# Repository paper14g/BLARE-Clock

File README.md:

# BLARE-Clock
This is my first ever Hack Club project! I should have chosen keeb because this is intermediate, but it is what it is.

this is CatClock, a clock that looks like a cat! except a screeching cat that will wake you up. I used Onshape to do the CAD designing work and I used Arduino IDE in order to code the firmware for the clock that will tell the time. Since I don't have a physical kit at the time of this typing, I will hope that it works first try. CAD designing was tricky at first because I never used it before. It took about 6-7 hours total and It was definitely very tricky.

This is my schematic, which shows an idea of how the parts are connected

This is my PCB, which will be custom made to fit my clock

As you can see, the PCB is held up by the supports inside the case and fit snugly in there with some screws to keep in place. The screen will also be inserted into a slot with a small hole behind it for connecting the the PCB.

There was some AI usage to assist me with KiCad footprint troubleshooting, OnShape tools, and some of the coding since I am unfamiliar with the coding language.

ONSHAPE LINK: https://cad.onshape.com/documents/35f3ca1c154542e0a4ea4d61/w/57b5bd0aad0669b366a0d6c3/e/0ef1ebbdd80ca3363562ccff?renderMode=0&uiState=6ac0b07b7f23611b255fec3d
 
I believe the guide asks me to put my Bill Of Materials here, so it's just a copy and paste.

|Designator|Quantity|Component Name|Footprint|Sourcing Link|
|---|---|---|---|---|
|U1|1|XIAO ESP32-C3|foot:XIAO-ESP32-C3-DIP|https://www.seeedstudio.com/Seeed-XIAO-ESP32C3-p-5431.html?srsltid=AU7gw4VDwjUAIm7gTielzF3R162CpobM-U2K9dWKoW9xlxCvq-3HqC8obDw
|SW1,SW2,SW3,SW4|4|Cherry MX Compatible Key Switch|switch:SW_Cherry_MX_1.00u_PCB|https://panda-mousepads.com/products/cherry-mx-mechanical-keyboard-switches-3-pin?variant=40930875670691&country=US&currency=USD&utm_medium=product_sync&utm_source=google&utm_content=sag_organic&utm_campaign=sag_organic&srsltid=AU7gw4UjE_LDTER6We5ZA6FkqacR6w-Ml-_MZT-fGag7CERpbxS0HlY9h4A
|J1|1|8-Pin 2.54mm Female Header Socket|connector:PinSocket_1x08_P2.54mm_Vertical|https://www.aliexpress.us/item/3256807486796996.html?spm=a2g0o.productlist.main.3.5654RBBuRBBuQy&algo_pvid=d6e48885-06fc-4b73-9e46-34dd52416a54&algo_exp_id=d6e48885-06fc-4b73-9e46-34dd52416a54-2&pdp_ext_f=%7B%22order%22%3A%22895%22%2C%22eval%22%3A%221%22%2C%22fromPage%22%3A%22search%22%7D&pdp_npi=6%40dis%21USD%212.60%211.09%21%21%212.60%211.09%21%402101ef5e17900453187957766e0eda%2112000041751476406%21sea%21US%210%21ABX%211%210%21n_tag%3A-29910%3Bd%3A982aa020%3Bm03_new_user%3A-29895%3BpisId%3A5000000210788688&curPageLogUid=JY7H0YBLu0v3&utparam-url=scene%3Asearch%7Cquery_from%3A%7Cx_object_id%3A1005007673111748%7C_p_origin_prod%3A
|BZ1|1|5V Passive Buzzer (12mm)|buzzer:Buzzer_12x9.5RM7.6|https://www.aliexpress.us/item/3256812304653037.html?spm=a2g0o.productlist.main.2.7167bTGybTGyND&algo_pvid=3d12822e-bb3b-4dd3-806f-8355b4d0be10&algo_exp_id=3d12822e-bb3b-4dd3-806f-8355b4d0be10-1&pdp_ext_f=%7B%22order%22%3A%2214%22%2C%22eval%22%3A%221%22%2C%22fromPage%22%3A%22search%22%7D&pdp_npi=6%40dis%21USD%214.26%211.09%21%21%2128.33%217.20%21%402103094f17900453807931080e130e%2112000058544450596%21sea%21US%210%21ABX%211%210%21n_tag%3A-29910%3Bd%3A982aa020%3Bm03_new_user%3A-29895%3BpisId%3A5000000210788678&curPageLogUid=0Z9NItkvW6ou&utparam-url=scene%3Asearch%7Cquery_from%3A%7Cx_object_id%3A1005012490967789%7C_p_origin_prod%3A
|J1|1|1.3 Inch Rectangular TFT LCD Module|connector:PinSocket_1x08_P2.54mm_Vertical|https://www.aliexpress.us/item/3256809161612031.html?spm=a2g0o.productlist.main.2.7c30OCHbOCHbqt&algo_pvid=e0094769-9c7d-42a3-a7c9-ebd94f11fb5c&algo_exp_id=e0094769-9c7d-42a3-a7c9-ebd94f11fb5c-1&pdp_ext_f=%7B%22order%22%3A%221138%22%2C%22eval%22%3A%221%22%2C%22fromPage%22%3A%22search%22%7D&pdp_npi=6%40dis%21USD%2171.88%2127.94%21%21%21478.56%21186.02%21%402101d9ef17900458449312800e0edc%2112000048828156242%21sea%21US%210%21ABX%211%210%21n_tag%3A-29910%3Bd%3A982aa020%3Bm03_new_user%3A-29895%3BpisId%3A5000000210788678&curPageLogUid=rcA0dcdMAjqR&utparam-url=scene%3Asearch%7Cquery_from%3A%7Cx_object_id%3A1005009347926783%7C_p_origin_prod%3A
|Hardware|4|M3 Brass Heat-Set Inserts & Screws|4.7mm CAD Hole|https://www.aliexpress.us/item/2255800046543591.html
|Screws (Short)|4|M3 x 8mm Button Head Machine Screws|M3 Clearance Hole|https://www.aliexpress.us/item/3256806191432536.html?spm=a2g0o.productlist.main.20.8e105e55iEFuXx&utparam-url=scene%3Asearch%7Cquery_from%3Apc_back_same_best%7Cx_object_id%3A1005006377747288%7C_p_origin_prod%3A&algo_pvid=7987ab63-8d65-465a-ab5c-b03ca118e8df&algo_exp_id=7987ab63-8d65-465a-ab5c-b03ca118e8df&pdp_ext_f=%7B%22order%22%3A%222140%22%2C%22fromPage%22%3A%22search%22%7D&pdp_npi=6%40dis%21USD%210.76%210.53%21%21%215.03%213.52%21%402103094f17900462549591222e1350%2112000036956444828%21sea%21US%210%21ABX%211%210%21n_tag%3A-29910%3Bd%3A73118c74%3Bm03_new_user%3A-29895&gatewayAdapt=4itemAdapt
|Screws (Long)|4|M3 x 16mm Button Head Machine Screws|M3 Clearance Hole|https://www.aliexpress.us/item/2251832772825104.html?spm=a2g0o.productlist.main.2.7e535d68fF4aoG&algo_pvid=b0ebe1dd-e0fd-461d-bdbb-e06f6866e78d&algo_exp_id=b0ebe1dd-e0fd-461d-bdbb-e06f6866e78d-1&pdp_ext_f=%7B%22order%22%3A%22308%22%2C%22eval%22%3A%221%22%2C%22fromPage%22%3A%22search%22%7D&pdp_npi=6%40dis%21USD%212.85%211.09%21%21%2118.96%217.24%21%402101dedf17900463106434580e10ea%2166368903762%21sea%21US%210%21ABX%211%210%21n_tag%3A-29910%3Bd%3A982aa020%3Bm03_new_user%3A-29895%3BpisId%3A5000000210788688&curPageLogUid=jL92MpLTxxYn&utparam-url=scene%3Asearch%7Cquery_from%3A%7Cx_object_id%3A32959139856%7C_p_origin_prod%3A
|Case|1|Custom 3D Printed Enclosure|/CAD/catclockCAD.step|N/A (Self-Designed)

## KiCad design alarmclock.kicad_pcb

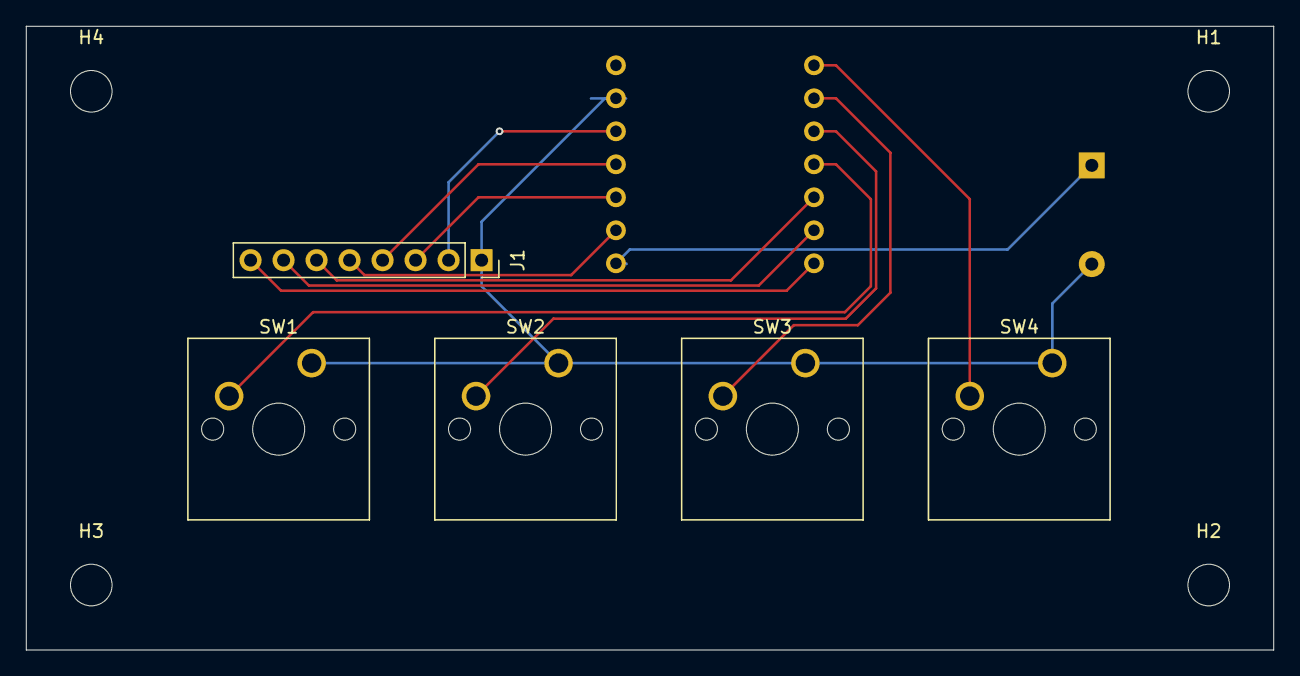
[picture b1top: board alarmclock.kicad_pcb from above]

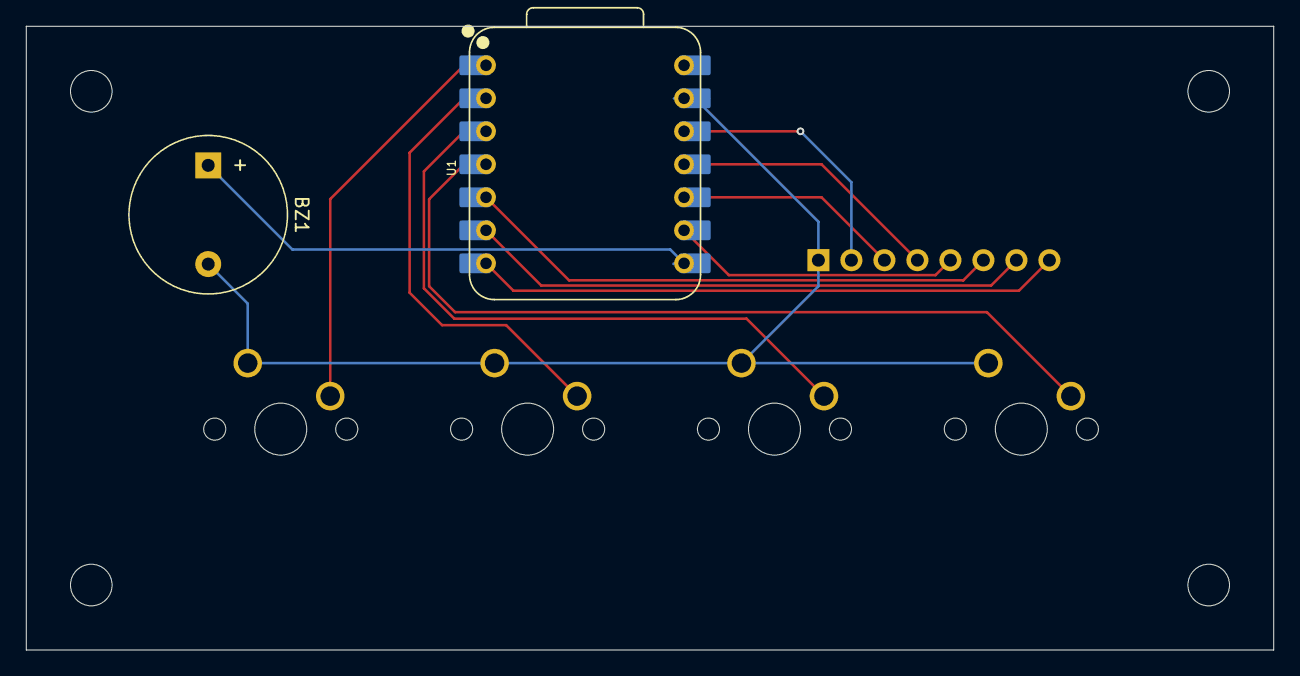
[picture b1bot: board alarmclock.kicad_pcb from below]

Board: 2 copper layers, 96.0 x 48.0 mm, 11 parts (2 on the bottom side), 13 nets.

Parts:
BZ1: Buzzer; Buzzer_12x9.5RM7.6
H1, H2, H3, H4: MountingHole; MountingHole_3.2mm_M3
J1: Conn_01x08; PinSocket_1x08_P2.54mm_Vertical
SW1, SW2, SW3, SW4: SW_Push; SW_Cherry_MX_1.00u_PCB
U1: XIAO-ESP32-C3-SMD; XIAO-ESP32-C3-DIP

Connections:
+3.3V: J1.2, U1.12 (3V3_OUT)
/BL: J1.8, U1.7 (D6)
/CS: J1.7, U1.6 (D5)
/DC: J1.6, U1.5 (D4)
/RST: J1.5, U1.9 (D8)
/SCL: J1.3, U1.10 (D9/BOOT)
/SDA: J1.4, U1.11 (D10)
GND: BZ1.2 (-), J1.1, SW1.1, SW2.1, SW3.1, SW4.1, U1.13 (GND)
unnamed: BZ1.1 (+), U1.8 (D7)
unnamed: SW4.2, U1.1 (D0)
unnamed: SW3.2, U1.2 (D1)
unnamed: SW2.2, U1.3 (D2)
unnamed: SW1.2, U1.4 (D3)
